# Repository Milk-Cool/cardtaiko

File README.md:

# card::taiko
osu!taiko simulator in a card form-factor!

## what this is
this is an RP2040-Zero based device that is made for simulating osu!taiko as closely as i was able to make it. it comes with capacitive touch buttons specifically shaped for taiko, a 320x170 display, an SD card reader, a speaker and a battery. you can also emulate a keyboard to play taiko-based games on your PC.

## how do i use it?
you'll have to build one yourself!! you can see `bom.xml` for the list of parts, and all the PCBs and modelsn as well as the firmware can also be found in this repository. then, you can convert and upload songs to an sd card using the [online tool](https://milk-cool.github.io/cardtaiko/). you have to put the songs in `/taiko` on the SD card. then, boot up the device, select your song and have fun!! (you can pause at any time by pressing BOOTSEL on the board.)

for navigation, you can use the outer buttons to switch between options, the inner left one to go back and the inner right one to select.

### building it
there are a few unmarked headers on the pcb. the one closest to the RP2040-Zero is where the display goes, the one in the upper left corner is for the SD card reader, and the four small ones all around the bottom part are where the 1x1 headers go in for the capacitive touch board. speaking of which, you also have to solder in 4 1MOhm resistors near the pins so that capactive touch works.

> important: see the touch board to make sure everything lines up!!

### using the website
the interface is very simple: upload your .osz files, wait for the button to become active (that means that [ffmpeg](https://ffmpeg.org/) has loaded) and click convert!! evrything happens in your browser so it shouldn't take too long to finish.

## why this was made
i am a huge fan of both taiko no tatsujin and osu!taiko, and also the [cardputer](https://shop.m5stack.com/products/m5stack-cardputer-adv-version-esp32-s3), which is why i decided it might be a fun idea to make a device that would let you play taiko on the go. and i also thought people might find the idea interesting as well :D

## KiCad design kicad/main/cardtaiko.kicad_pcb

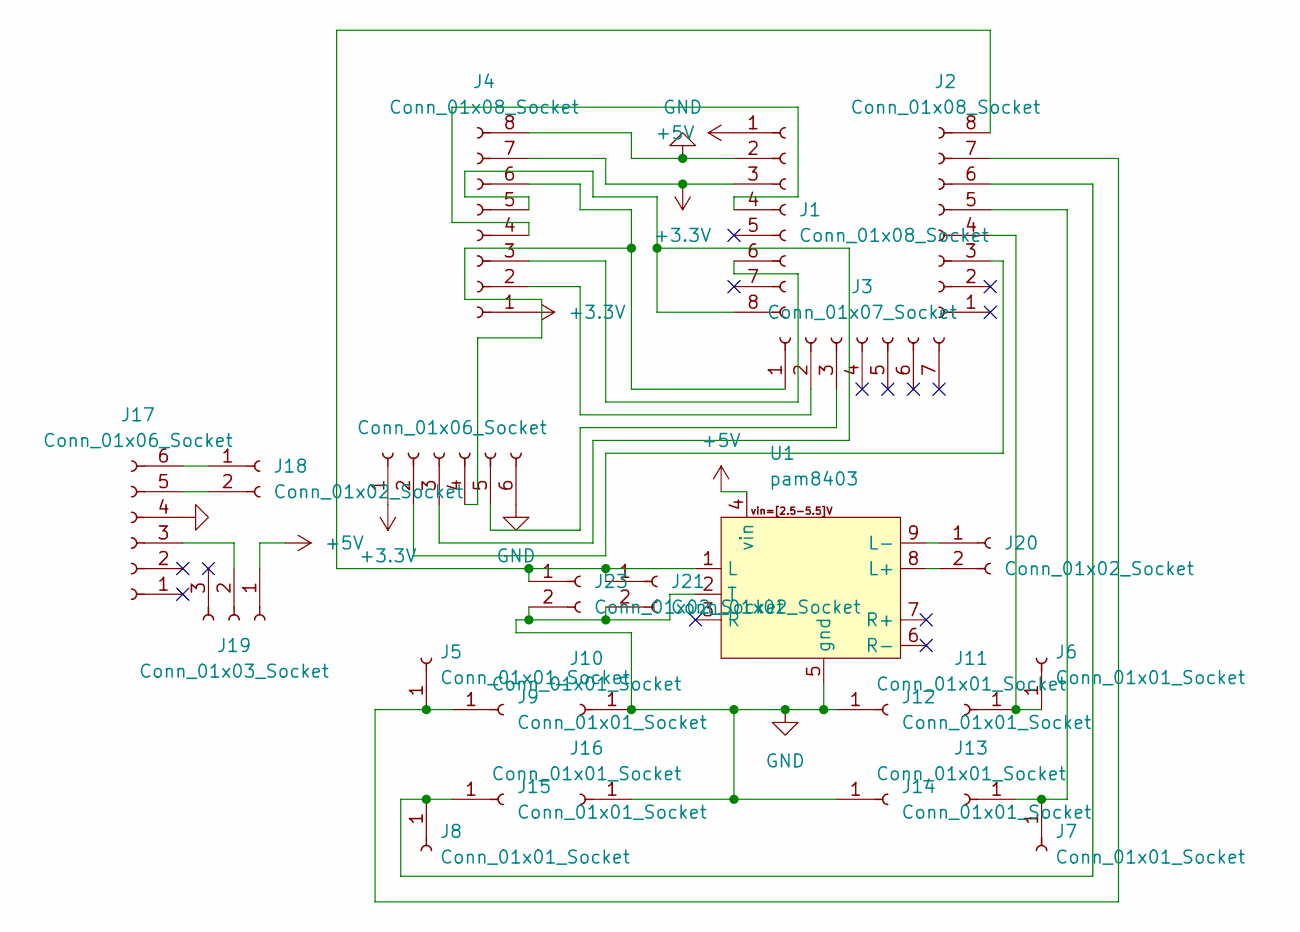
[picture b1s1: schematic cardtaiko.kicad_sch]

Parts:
J1, J2, J4: Conn_01x08_Socket; PinHeader_1x08_P2.54mm_Vertical
J3: Conn_01x07_Socket; PinHeader_1x07_P2.54mm_Vertical
J5, J6, J7, J8, J9, J10, J11, J12, J13, J14, J15, J16: Conn_01x01_Socket; PinHeader_1x01_P2.54mm_Vertical
J17: Conn_01x06_Socket; TP4056-18650
J18, J20, J21, J23: Conn_01x02_Socket; PinHeader_1x02_P2.54mm_Vertical
J19: Conn_01x03_Socket; 1p2t
J22: Conn_01x06_Socket; PinHeader_1x06_P2.54mm_Vertical
U1: pam8403

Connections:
+3.3V: J1.3, J4.1, J4.7, J22.1
+5V: J1.1, J19.1, U1.4 (vin)
GND: J1.2, J4.8, J10.1 (Pin_1_1), J12.1 (Pin_1_1), J14.1 (Pin_1_1), J16.1 (Pin_1_1), J17.4, J21.2, J22.6, J23.2, U1.2 (T), U1.5 (gnd)
unnamed: J1.4, J4.4
unnamed: J1.6, J4.3
unnamed: J1.8, J4.5, J22.3
unnamed: J2.3, J22.2
unnamed: J2.7, J5.1 (Pin_1_1), J9.1 (Pin_1_1)
unnamed: J2.8, J21.1, J23.1, U1.1 (L)
unnamed: J3.2, J4.2
unnamed: J2.4, J6.1 (Pin_1_1), J11.1 (Pin_1_1)
unnamed: J2.5, J7.1 (Pin_1_1), J13.1 (Pin_1_1)
unnamed: J2.6, J8.1 (Pin_1_1), J15.1 (Pin_1_1)
unnamed: J17.3, J19.2
unnamed: J17.5, J18.2
unnamed: J17.6, J18.1
unnamed: J20.1, U1.9 (L-)
unnamed: J20.2, U1.8 (L+)
unnamed: J3.1, J4.6, J22.4
unnamed: J3.3, J22.5

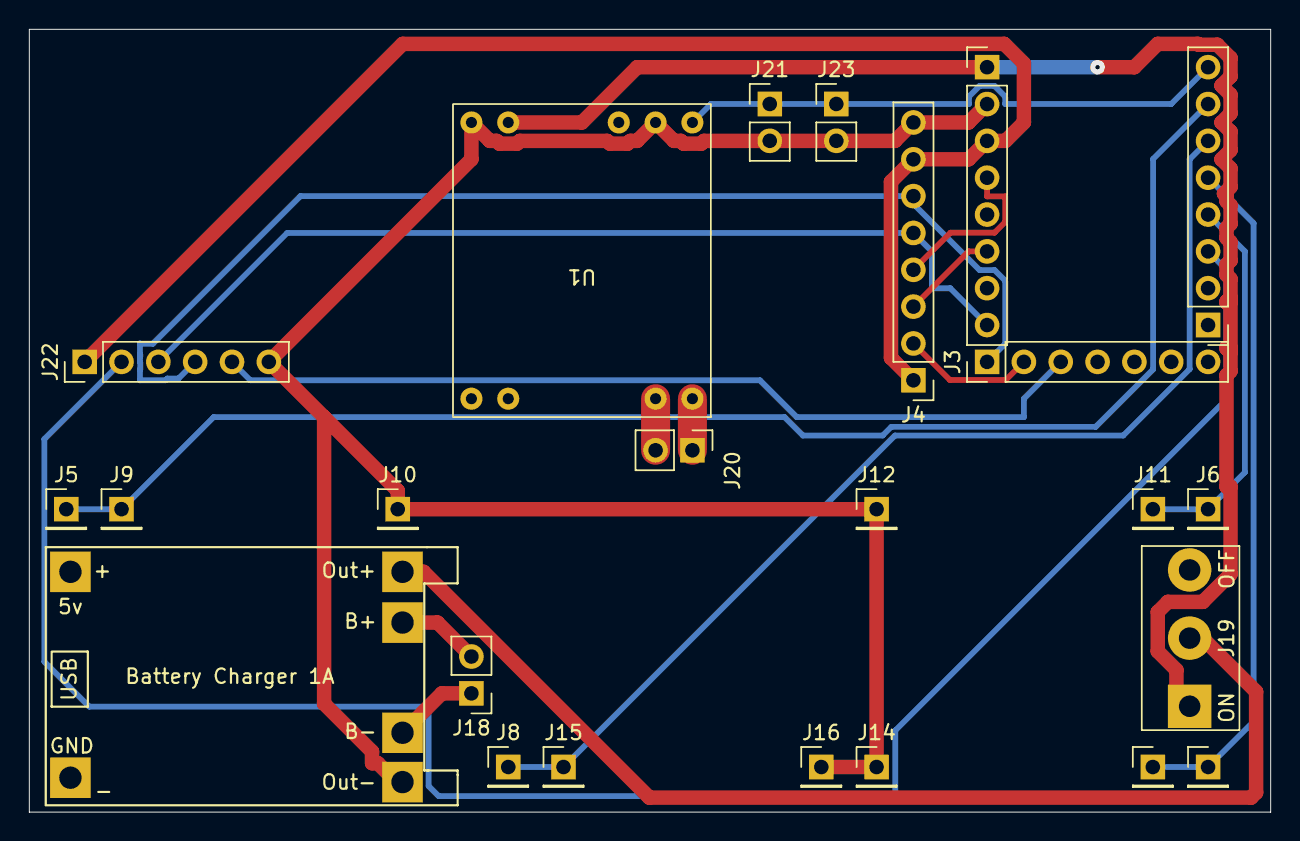
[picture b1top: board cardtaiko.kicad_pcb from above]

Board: 2 copper layers, 85.6 x 54.0 mm, 24 parts (0 on the bottom side), 20 nets.

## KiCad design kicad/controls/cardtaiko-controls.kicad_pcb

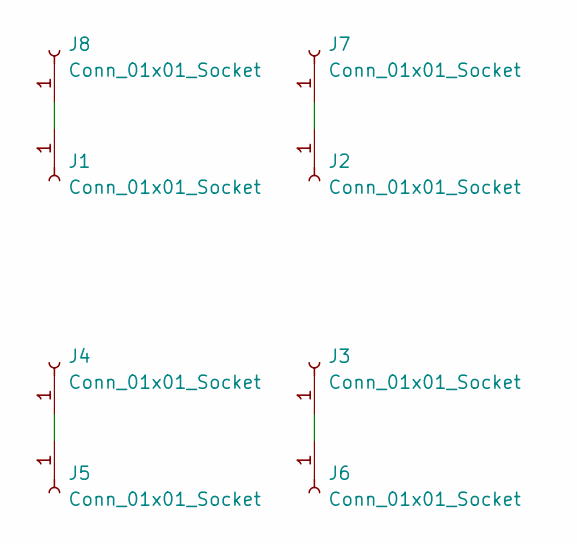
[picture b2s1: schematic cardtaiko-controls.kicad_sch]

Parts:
J1, J2, J3, J4: Conn_01x01_Socket; PinHeader_1x01_P2.54mm_Vertical
J5: Conn_01x01_Socket; Don Left
J6: Conn_01x01_Socket; Don Right
J7: Conn_01x01_Socket; Kat Right
J8: Conn_01x01_Socket; Kat Left

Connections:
unnamed: J1.1 (Pin_1_1), J8.1 (Pin_1_1)
unnamed: J2.1 (Pin_1_1), J7.1 (Pin_1_1)
unnamed: J3.1 (Pin_1_1), J6.1 (Pin_1_1)
unnamed: J4.1 (Pin_1_1), J5.1 (Pin_1_1)

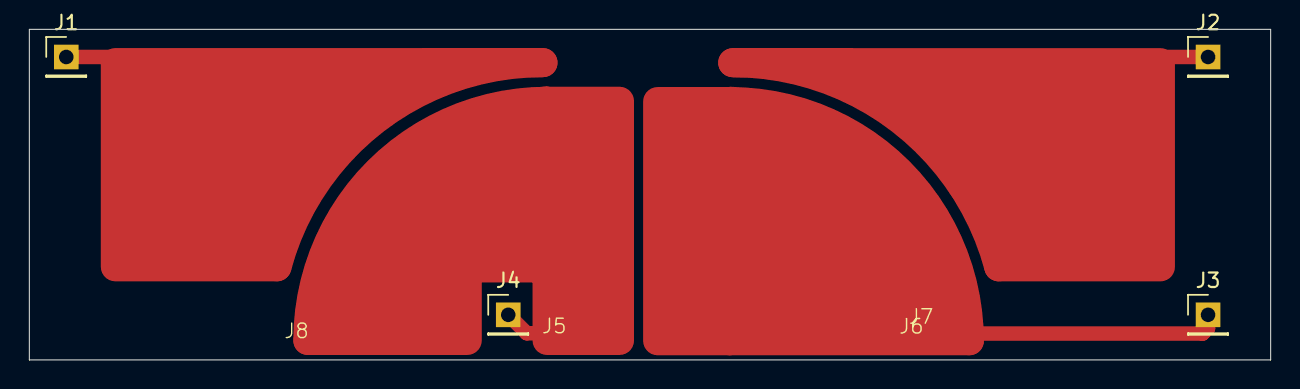
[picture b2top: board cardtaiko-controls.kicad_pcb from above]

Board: 2 copper layers, 85.6 x 22.8 mm, 8 parts (0 on the bottom side), 4 nets.

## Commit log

2026-05-07 st7789 display
2026-05-07 IT WORKS
2026-05-08 osu level parsing!!
2026-05-09 switch to lgfx
2026-05-09 optimize rendering
2026-05-09 change notes rendering
2026-05-09 lvgl magic!!!
2026-05-09 increase speed
2026-05-10 yayayayya input works!!
2026-05-10 big notes
2026-05-10 drumrolls rendering
2026-05-10 yayayayay drumrolls are now handled in input!!
2026-05-10 add rating text
2026-05-10 more accurate combo bonus calculation
2026-05-10 oops
2026-05-10 clearly, i am way too tired for this
2026-05-11 even more accurate score calculation + score display
2026-05-11 denden notes (minus the target amt)
2026-05-11 denden targets
2026-05-11 small visual fix
2026-05-11 menus!!
2026-05-11 menu wrap handling
2026-05-11 fix bug with level loading
2026-05-12 fix combo bonus calculation
2026-05-13 it just doesn't work :(( i'm still gonna commit everything tho
2026-05-14 capacitive touch, audio rewrite
2026-05-14 remove debug prints
2026-05-15 backup
2026-05-15 this should work
2026-05-15 :yay: it works again!! and also added led support
2026-05-15 add to captouch threshold
2026-05-15 i mean i guess it works
2026-05-16 add pausing
2026-05-16 endscreens
2026-05-16 keyboard mode
2026-05-16 change led brigthness to 40
2026-05-16 change threshold again
2026-05-16 adjust the sensitivity again
2026-05-17 update sensitivity AGAIN
2026-05-17 a couple fixes
2026-05-17 change audio volume
2026-05-17 change thresholds AGAIN!!
2026-05-17 ..and again :sk:
2026-05-17 add score to results screen
2026-05-19 web converter
2026-05-20 a couple more firmware fixes
2026-05-20 wembgh
2026-06-01 add BOM
2026-06-01 add the zine
2026-06-01 whoops
2026-06-01 add the readme
2026-06-01 add kicad files and 3d models
2026-06-01 add precompiled firmware file
2026-06-01 add navigation instructions bc i forgor :skull:
